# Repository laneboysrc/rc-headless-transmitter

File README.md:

# Smartphone / Web browser configurable RC transmitter

This project implements a 2.4 GHz RC transmitter using the NRF24L01+ wireless module and the STM32F103C8T6 micro-controller.

The term *headless* comes from the IT industry, where a headless system is one that does not provide a user interface itself, but is rather configured remotely. Within this project, *headless* means that the transmitter does not have a display or buttons for configuration. It relies on remote configuration through a web-browser running on a Smartphone, Tablet or computer.

The motivation for this project was to upgrade old AM/FM RC transmitter hardware, and to turn a cheap RC simulator into a fully operational transmitter that supports multiple models.

By keeping the user interface for configuration out of the transmitter, we don't need to perform complicated mechanical modifications to add a display and buttons. We only replace the old electronics with a modern 32 bit ARM micro-controller and a reliable 2.4 GHz transceiver wired on a prototyping board.

The transmitter is currently compatible with HobbyKing HKR3000 and HKR3100 receivers, as well as the [LANE Boys RC nrf24le01-rc](https://github.com/laneboysrc/nrf24l01-rc) DIY receivers. It runs off a 1S Li-Ion battery.

## How it works

The *headless transmitter* works like any low-end 2.4 GHz RC system on the market: power it on, and use it with the model you have it setup for.

However, unlike low-end transmitters, the *headless transmitter* supports advanced features like expo, mixing, failsafe and more.

In order to configure those features, you need to use a web-browser on your Smartphone, Tablet or computer.

To be able to connect your Smartphone to the transmitter, we need to translate between different radio protocols: The transmitter uses a proprietary RF protocol, while the Smartphone supports Wi-Fi. This translation takes place in a small, external box called *configurator*.

When you want to configure your *headless transmitter*, you turn the *configurator* on, connect your phone to the Wi-Fi access-point the *configurator* provides, and launch the configuration web-app to perform the configuration. When you are done, the changes are automatically saved in the transmitter and persist over power cycles.

The *configurator* is built from an **Orange Pi Zero**, with an extra RF module for the connection to the *headless transmitter*.

The Smartphone has a large amount of persistent memory. This allows us to store configurations for multiple models. When we want to reconfigure the transmitter for another model, we simply download the model configuration configuration into the *headless transmitter*. This only takes a few seconds.

The power consumption of the transmitter is low: A single 800 mAh Li-Ion battery keeps the transmitter running for approximately 15 hours. The *configurator* is only used rarely and can be powered from a suitable power bank.

## Cost

When sourcing the modules from China, a transmitter can be built for less than USD 10. The *configurator* hardware cost is less than USD 20. You only need one *configurator*, regardless of how many *headless transmitters* you have.

## Getting started

Please consult the [INSTALL.md](INSTALL.md) file for instructions.

The [docs/](docs) folder contains various documents explaining details for the architecture.

The *headless transmitters* hardware is described in the [transmitter/](transmitter/) folder.

The *configurator* is based on the Orange Pi Zero. Its hardware documentation resides in
[configurator/orangepizero/HARDWARE.md](configurator/orangepizero/HARDWARE.md).

The *web-app* can be accessed from [https://laneboysrc.github.io/rc-headless-transmitter](https://laneboysrc.github.io/rc-headless-transmitter)

## WORK IN PROGRESS

This project is not finished yet. Refer to the [TODO](TODO.md) list for items that we plan to implement in the future.

At the moment the project has only been tested on Android using Chrome and Firefox, and on PCs running Chrome or Firefox.

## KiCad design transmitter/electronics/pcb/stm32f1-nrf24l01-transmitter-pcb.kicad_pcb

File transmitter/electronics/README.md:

This folder contains the schematics and layout of the *headless transmitter* hardware.

[BOM.txt](BOM.txt) contains a list of all components.

The project is made using [KiCad](http://kicad-pcb.org/). For convenience the schematics are also available in [PDF format](stm32f1-nrf24l01-transmitter.pdf).

Note that the PCB designs are not actual circuit board designs, but rather meant to be built on a [Perfboard](https://en.wikipedia.org/wiki/Perfboard).

There are different variants that we adapted to suit different transmitters we modified.

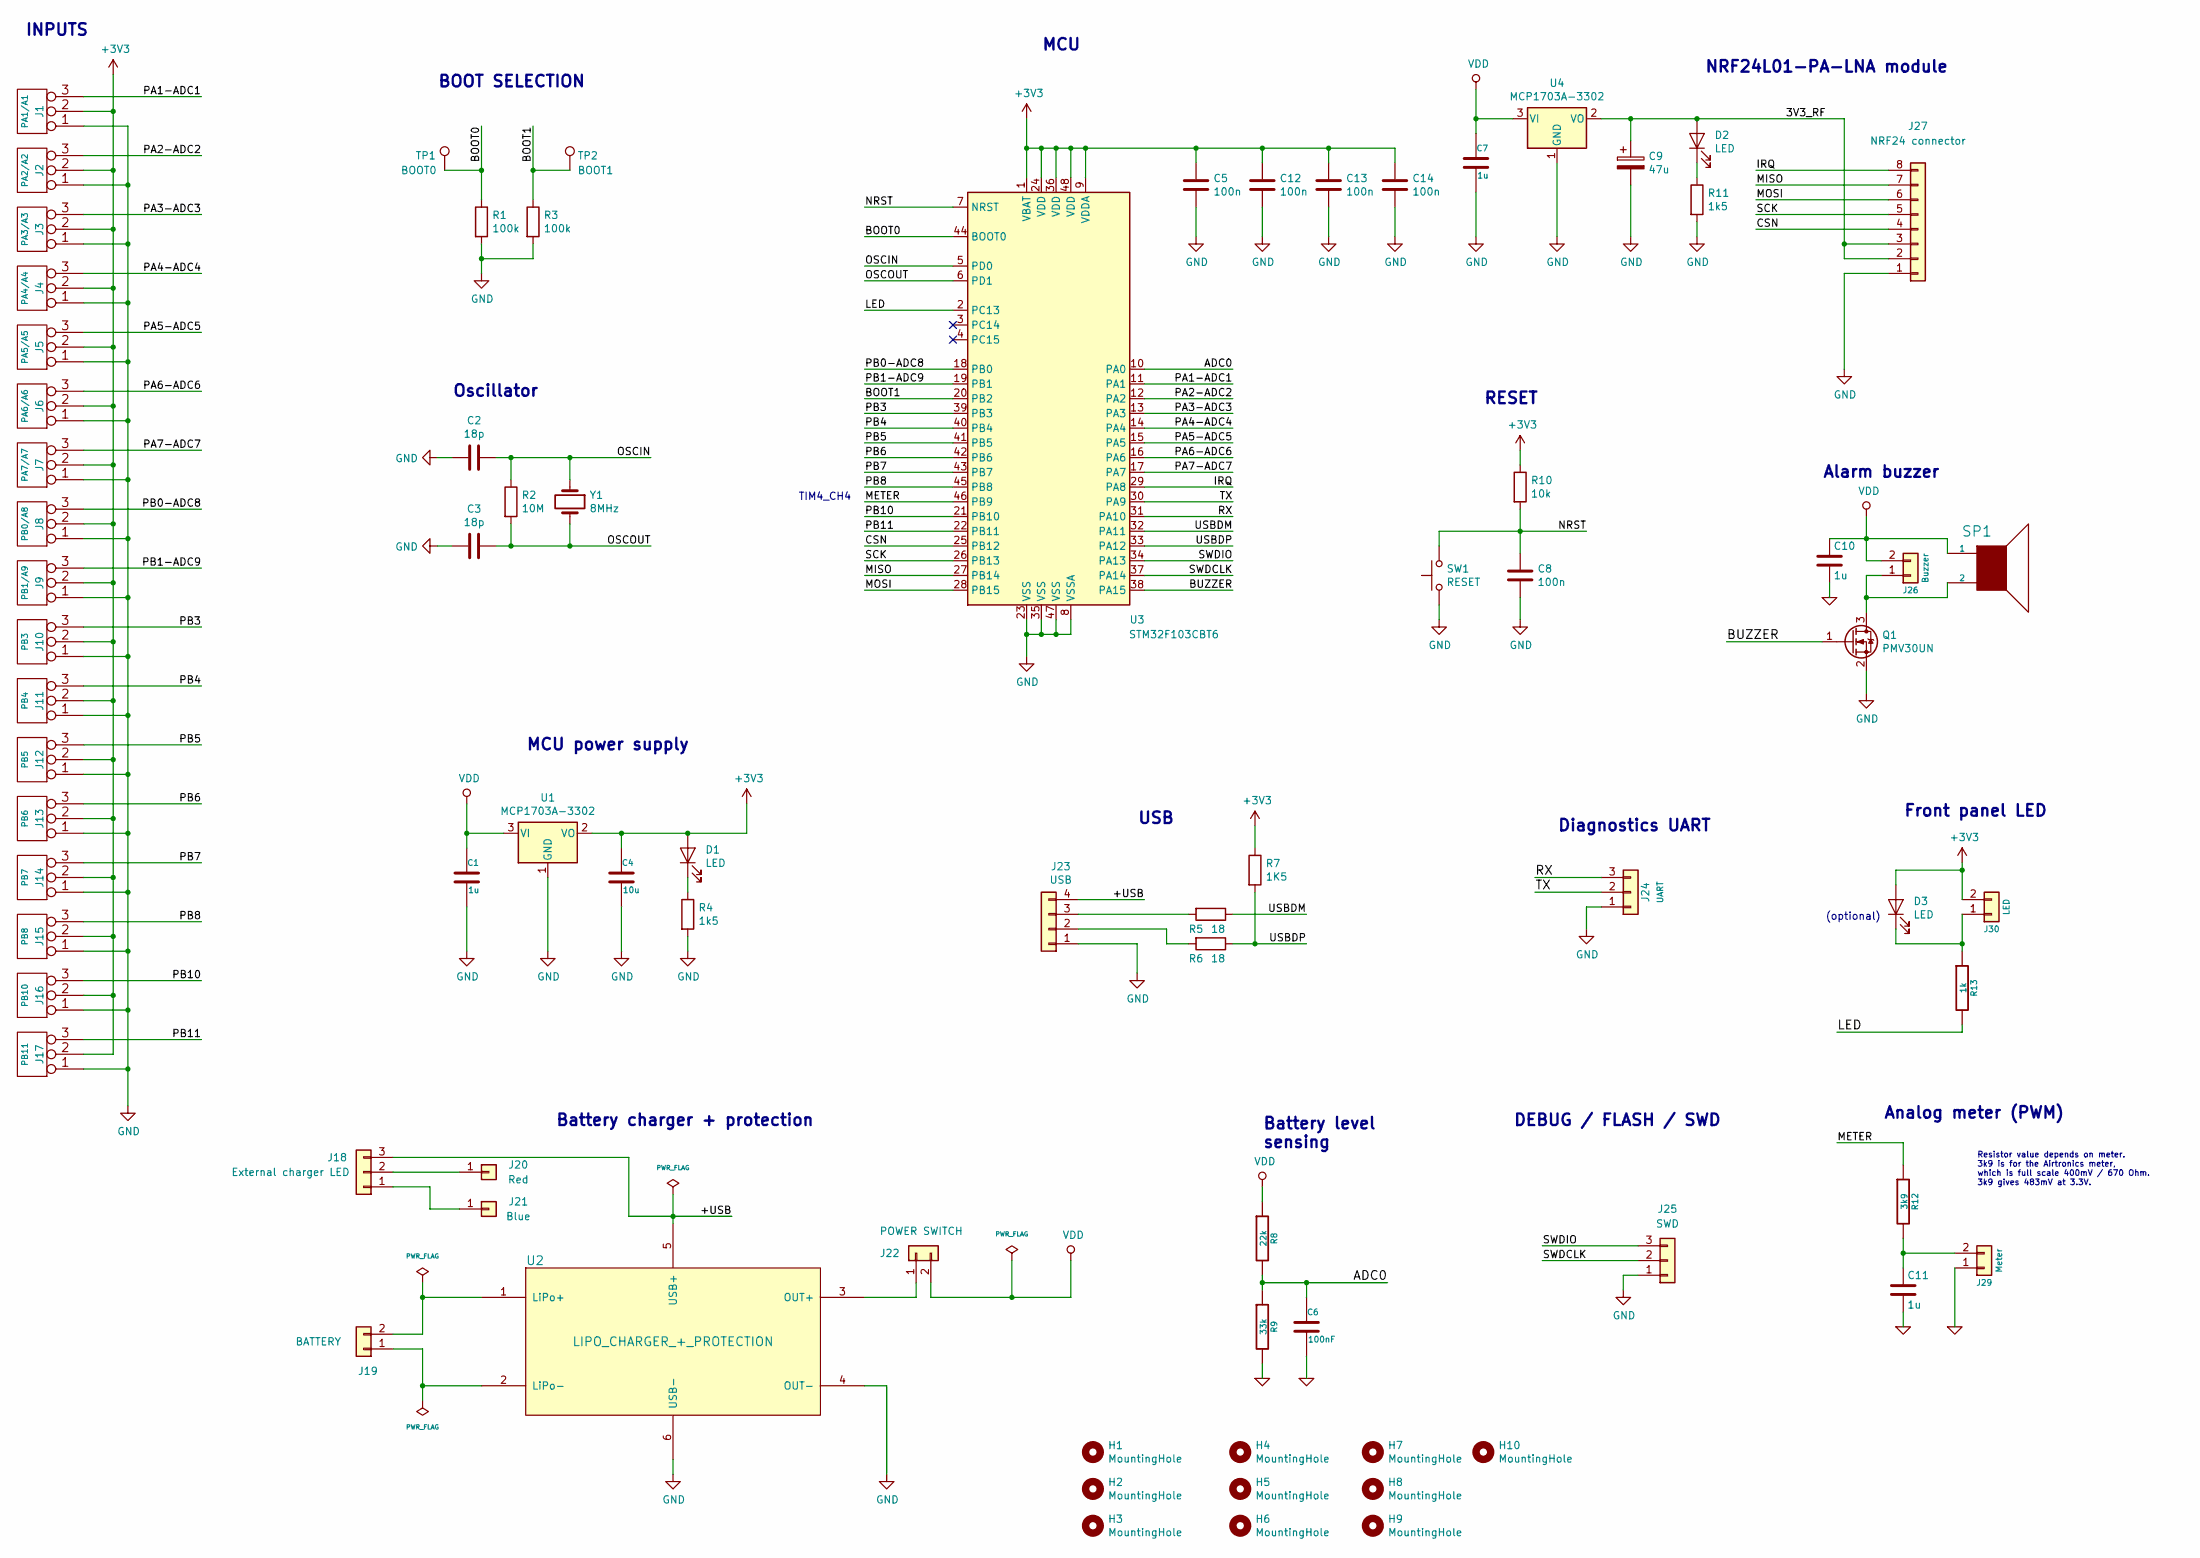
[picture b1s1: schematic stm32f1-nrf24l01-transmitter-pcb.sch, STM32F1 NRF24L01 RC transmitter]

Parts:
C1, C7, C10, C11: 1u; C_0805_2012Metric_Pad1.15x1.40mm_HandSolder
C2, C3: 18p; C_0603_1608Metric_Pad1.05x0.95mm_HandSolder
C4: 10u; C_0805_2012Metric_Pad1.15x1.40mm_HandSolder
C5, C8, C12, C13, C14: 100n; C_0603_1608Metric_Pad1.05x0.95mm_HandSolder
C6: 100nF; C_0805_2012Metric_Pad1.15x1.40mm_HandSolder
C9: 47u; C_0805_2012Metric_Pad1.15x1.40mm_HandSolder
D1, D2, D3: LED; LED_0805_2012Metric_Pad1.15x1.40mm_HandSolder
H1, H2, H3, H9, H10: MountingHole; MountingHole_3.2mm_M3_DIN965
H4, H5, H6, H7, H8: MountingHole; MountingHole_2.7mm_M2.5_DIN965
J1: PA1/A1; JST_XH_B3B-XH-A_1x03_P2.50mm_Vertical
J2: PA2/A2; JST_XH_B3B-XH-A_1x03_P2.50mm_Vertical
J3: PA3/A3; JST_XH_B3B-XH-A_1x03_P2.50mm_Vertical
J4: PA4/A4; JST_XH_B3B-XH-A_1x03_P2.50mm_Vertical
J5: PA5/A5; JST_XH_B3B-XH-A_1x03_P2.50mm_Vertical
J6: PA6/A6; JST_XH_B3B-XH-A_1x03_P2.50mm_Vertical
J7: PA7/A7; JST_XH_B3B-XH-A_1x03_P2.50mm_Vertical
J8: PB0/A8; JST_XH_B3B-XH-A_1x03_P2.50mm_Vertical
J9: PB1/A9; JST_XH_B3B-XH-A_1x03_P2.50mm_Vertical
J10: PB3; JST_XH_B3B-XH-A_1x03_P2.50mm_Vertical
J11: PB4; JST_XH_B3B-XH-A_1x03_P2.50mm_Vertical
J12: PB5; JST_XH_B3B-XH-A_1x03_P2.50mm_Vertical
J13: PB6; JST_XH_B3B-XH-A_1x03_P2.50mm_Vertical
J14: PB7; JST_XH_B3B-XH-A_1x03_P2.50mm_Vertical
J15: PB8; JST_XH_B3B-XH-A_1x03_P2.50mm_Vertical
J16: PB10; JST_XH_B3B-XH-A_1x03_P2.50mm_Vertical
J17: PB11; JST_XH_B3B-XH-A_1x03_P2.50mm_Vertical
J18: External charger LED; JST_XH_B3B-XH-A_1x03_P2.50mm_Vertical
J19: BATTERY; JST_XH_B2B-XH-A_1x02_P2.50mm_Vertical
J20: Red; TestPoint_Pad_1.5x1.5mm
J21: Blue; TestPoint_Pad_1.5x1.5mm
J22: POWER SWITCH; JST_XH_B2B-XH-A_1x02_P2.50mm_Vertical
J23: USB; JST_XH_B4B-XH-A_1x04_P2.50mm_Vertical
J24: UART; PinHeader_1x03_P2.54mm_Vertical
J25: SWD; PinHeader_1x03_P2.54mm_Vertical
J26: Buzzer; JST_XH_B2B-XH-A_1x02_P2.50mm_Vertical
J27: NRF24 connector; JST_XH_B8B-XH-A_1x08_P2.50mm_Vertical
J29: Meter; JST_XH_B2B-XH-A_1x02_P2.50mm_Vertical
J30: LED; JST_XH_B2B-XH-A_1x02_P2.50mm_Vertical
Q1: PMV30UN; SOT-23_Handsoldering
R1, R3: 100k; R_0805_2012Metric_Pad1.15x1.40mm_HandSolder
R2: 10M; R_0805_2012Metric_Pad1.15x1.40mm_HandSolder
R4, R11: 1k5; R_0805_2012Metric_Pad1.15x1.40mm_HandSolder
R5, R6: 18; R_0805_2012Metric_Pad1.15x1.40mm_HandSolder
R7: 1K5; R_0805_2012Metric_Pad1.15x1.40mm_HandSolder
R8: 22k; R_0805_2012Metric_Pad1.15x1.40mm_HandSolder
R9: 33k; R_0805_2012Metric_Pad1.15x1.40mm_HandSolder
R10: 10k; R_0805_2012Metric_Pad1.15x1.40mm_HandSolder
R12: 3k9; R_0805_2012Metric_Pad1.15x1.40mm_HandSolder
R13: 1k; R_0805_2012Metric_Pad1.15x1.40mm_HandSolder
SP1: SPEAKER; MagneticBuzzer_PUI_AT-0927-TT-6-R
SW1: RESET; Tact switch 6x4x3
TP1: BOOT0; TestPoint_Pad_1.5x1.5mm
TP2: BOOT1; TestPoint_Pad_1.5x1.5mm
U1, U4: MCP1703A-3302; SOT-23_Handsoldering
U2: LIPO_CHARGER_+_PROTECTION; LiPo_charger_and_protection
U3: STM32F103CBT6; LQFP-48_7x7mm_P0.5mm
Y1: 8MHz; Crystal_SMD_5032-2Pin_5.0x3.2mm

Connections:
+3V3: C4.1, C5.1, C12.1, C13.1, C14.1, D1.2 (A), D3.2 (A), J1.2 (PM), J2.2 (PM), J3.2 (PM), J4.2 (PM), J5.2 (PM), J6.2 (PM), J7.2 (PM), J8.2 (PM), J9.2 (PM), J10.2 (PM), J11.2 (PM), J12.2 (PM), J13.2 (PM), J14.2 (PM), J15.2 (PM), J16.2 (PM), J17.2 (PM), J30.2, R7.1, R10.1, U1.2 (VO), U3.1 (VBAT), U3.9 (VDDA), U3.24 (VDD), U3.36 (VDD), U3.48 (VDD)
/3V3_RF: C9.1, D2.2 (A), J27.2, J27.3, U4.2 (VO)
/+USB: J18.3, J23.4, U2.5 (USB+)
/ADC0: C6.1, R8.2, R9.1, U3.10 (PA0)
/BOOT0: R1.1, TP1.1, U3.44 (BOOT0)
/BOOT1: R3.1, TP2.1, U3.20 (PB2)
/BUZZER: Q1.1 (G), U3.38 (PA15)
/CSN: J27.4, U3.25 (PB12)
/IRQ: J27.8, U3.29 (PA8)
/LED: R13.2, U3.2 (PC13)
/METER: R12.1, U3.46 (PB9)
/MISO: J27.7, U3.27 (PB14)
/MOSI: J27.6, U3.28 (PB15)
/NRST: C8.1, R10.2, SW1.2, U3.7 (NRST)
/OSCIN: C2.1, R2.1, U3.5 (PD0), Y1.1
/OSCOUT: C3.1, R2.2, U3.6 (PD1), Y1.2
/PA1-ADC1: J1.3, U3.11 (PA1)
/PA2-ADC2: J2.3, U3.12 (PA2)
/PA3-ADC3: J3.3, U3.13 (PA3)
/PA4-ADC4: J4.3, U3.14 (PA4)
/PA5-ADC5: J5.3, U3.15 (PA5)
/PA6-ADC6: J6.3, U3.16 (PA6)
/PA7-ADC7: J7.3, U3.17 (PA7)
/PB0-ADC8: J8.3, U3.18 (PB0)
/PB1-ADC9: J9.3, U3.19 (PB1)
/PB3: J10.3, U3.39 (PB3)
/PB4: J11.3, U3.40 (PB4)
/PB5: J12.3, U3.41 (PB5)
/PB6: J13.3, U3.42 (PB6)
/PB7: J14.3, U3.43 (PB7)
/PB8: J15.3, U3.45 (PB8)
/PB10: J16.3, U3.21 (PB10)
/PB11: J17.3, U3.22 (PB11)
/RX: J24.3, U3.31 (PA10)
/SCK: J27.5, U3.26 (PB13)
/SWDCLK: J25.2, U3.37 (PA14)
/SWDIO: J25.3, U3.34 (PA13)
/TX: J24.2, U3.30 (PA9)
/USBDM: R5.1, U3.32 (PA11)
/USBDP: R6.1, R7.2, U3.33 (PA12)
GND: C1.2, C2.2, C3.2, C4.2, C5.2, C6.2, C7.2, C8.2, C9.2, C10.2, C11.2, C12.2, C13.2, C14.2, J1.1, J2.1, J3.1, J4.1, J5.1, J6.1, J7.1, J8.1, J9.1, J10.1, J11.1, J12.1, J13.1, J14.1, J15.1, J16.1, J17.1, J23.1, J24.1, J25.1, J27.1, J29.1, Q1.2 (S), R1.2, R3.2, R4.2, R9.2, R11.2, SW1.1, U1.1 (GND), U2.4 (OUT-), U2.6 (USB-), U3.8 (VSSA), U3.23 (VSS), U3.35 (VSS), U3.47 (VSS), U4.1 (GND)
unnamed: C11.1, J29.2, R12.2
unnamed: D1.1 (K), R4.1
unnamed: D2.1 (K), R11.1
unnamed: D3.1 (K), J30.1, R13.1
unnamed: J18.1, J21.1
unnamed: J18.2, J20.1
unnamed: J19.1, U2.2 (LiPo-)
unnamed: J19.2, U2.1 (LiPo+)
unnamed: J22.1, U2.3 (OUT+)
unnamed: J23.2, R6.2
unnamed: J23.3, R5.2
unnamed: J26.1, Q1.3 (D), SP1.2
VDD: C1.1, C7.1, C10.1, J22.2, J26.2, R8.1, SP1.1, U1.3 (VI), U4.3 (VI)

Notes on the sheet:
Diagnostics UART
Front panel LED
Alarm buzzer
Analog meter (PWM)
Resistor value depends on meter. 3k9 is for the Airtronics meter, which is full scale 400mV / 670 Ohm. 3k9 gives 483mV at 3.3V.
USB
Battery level sensing
TIM4_CH4
(optional)
BOOT SELECTION
INPUTS
MCU
NRF24L01-PA-LNA module
MCU power supply
Battery charger + protection
Oscillator
RESET
DEBUG / FLASH / SWD

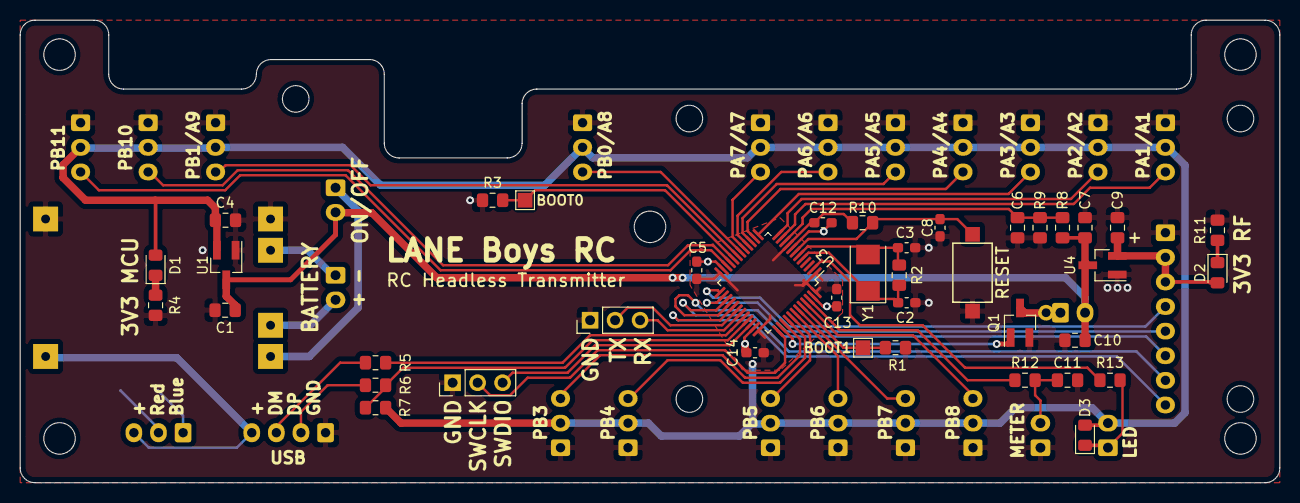
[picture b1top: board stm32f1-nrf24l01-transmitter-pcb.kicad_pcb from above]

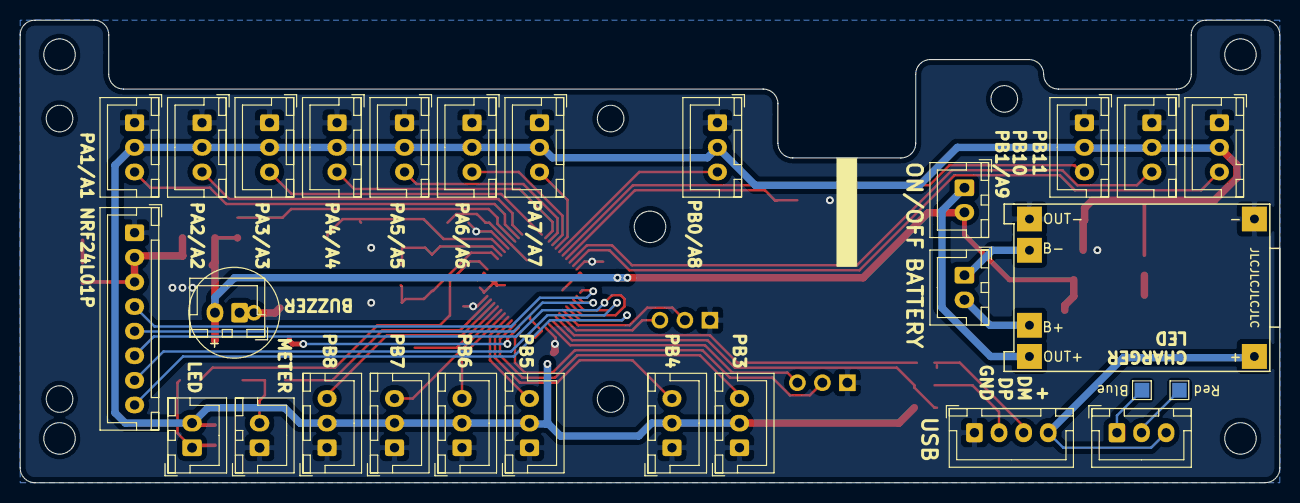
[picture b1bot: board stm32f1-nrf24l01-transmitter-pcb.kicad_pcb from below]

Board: 2 copper layers, 128.0 x 47.0 mm, 79 parts (29 on the bottom side), 54 nets.

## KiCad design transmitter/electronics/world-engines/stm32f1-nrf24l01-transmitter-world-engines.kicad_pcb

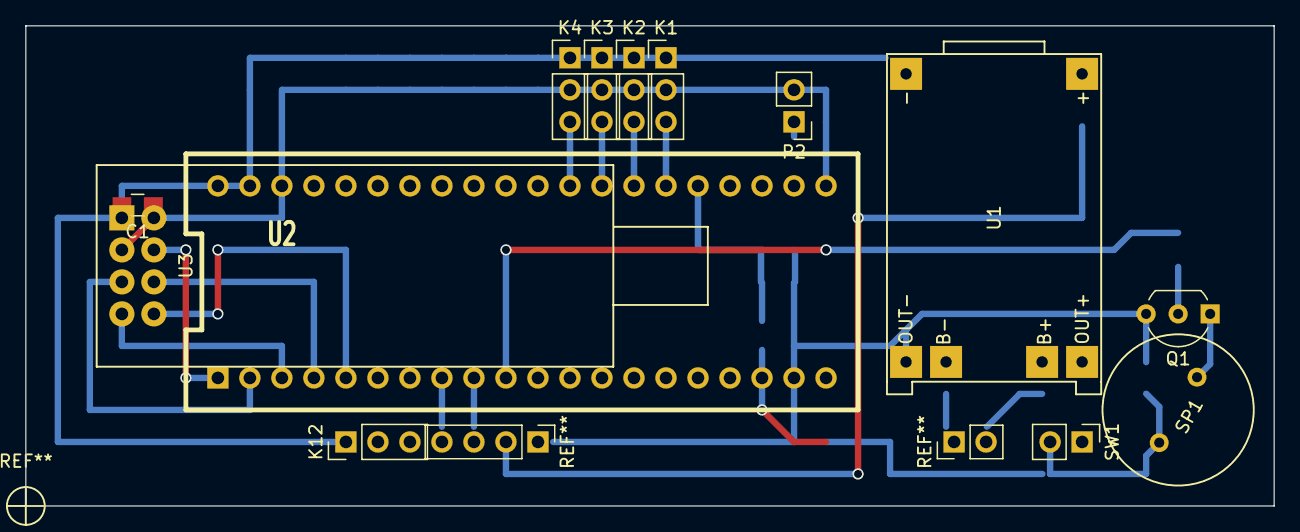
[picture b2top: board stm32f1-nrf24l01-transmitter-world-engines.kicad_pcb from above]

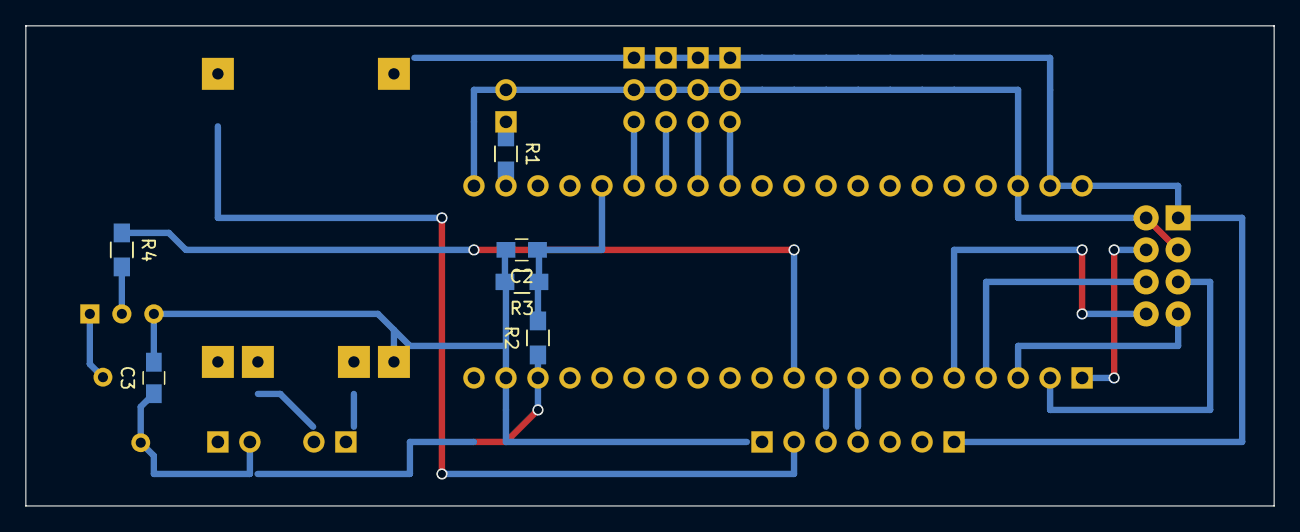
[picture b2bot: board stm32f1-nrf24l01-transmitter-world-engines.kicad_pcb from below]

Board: 2 copper layers, 99.1 x 38.1 mm, 19 parts (6 on the bottom side), 21 nets.

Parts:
C1, C3: 1u; C_0805_HandSoldering
C2: 100nF; C_0805_HandSoldering
K1, K2, K3, K4: CONN_3; Pin_Header_Straight_1x03_Pitch2.54mm
K12: UART; Pin_Header_Straight_1x03_Pitch2.54mm
P2: LED; Pin_Header_Straight_1x02_Pitch2.54mm
Q1: BC547B; TO-92_Inline_Wide
R1, R4: 1k; R_0805_HandSoldering
R2: 22k; R_0805_HandSoldering
R3: 33k; R_0805_HandSoldering
SP1: SPEAKER; Buzzer_passive
SW1: ON/OFF; Pin_Header_Straight_1x02_Pitch2.54mm
U1: LIPO_CHARGER_+_PROTECTION; LiPo_charger_and_protection
U2: STM32F103C8T6_DEV_BOARD; STM32F103C8T6
U3: NRF24L01P; NRF24L01P-PA-LNA

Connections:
/ADC0: C2.1, R2.2, R3.1, U2.25
/BUZZER: R4.1, U2.10
/CSN: U2.1, U3.4
/IRQ: U2.5, U3.8
/LED: R1.2, U2.22
/MISO: U2.3, U3.7
/MOSI: U2.4, U3.6
/PA1/ADC1: K1.3, U2.26
/PA2/ADC2: K2.3, U2.27
/PA3/ADC3: K3.3, U2.28
/PA4/ADC4: K4.3, U2.29
/RX: K12.2, U2.7
/SCK: U2.2, U3.5
/TX: K12.3, U2.6
GND: C1.2, C2.2, C3.2, K1.1, K2.1, K3.1, K4.1, K12.1, Q1.3, R3.2, U1.4, U2.19, U2.39, U2.40, U3.1
unnamed: P2.1, R1.1
unnamed: Q1.1, SP1.2
unnamed: Q1.2, R4.2
unnamed: SW1.1, U1.3
VCC: C1.1, K1.2, K2.2, K3.2, K4.2, P2.2, U2.21, U2.38, U3.2, U3.3
VDD: C3.1, R2.1, SP1.1, SW1.2, U2.18

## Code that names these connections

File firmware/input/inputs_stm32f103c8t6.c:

// Inputs available on the AliExpress STM32F103C8T6 board

#include <libopencm3/stm32/gpio.h>

#include <inputs.h>


const uint8_t adc_channel_selection[NUMBER_OF_ADC_CHANNELS] = {1, 2, 3, 4, 5, 6, 7, 8, 9, 0, 17};


const pcb_input_t pcb_inputs[MAX_TRANSMITTER_INPUTS] = {
    // Note: ADC0 is used for measuring the battery voltage, therefore it does
    // not appear in this list

    {.type = ANALOG_DIGITAL, .gpioport = GPIOA, .gpio = GPIO1, .adc_channel = 1,
     .pin_name = "PA1/ADC1"},

    {.type = ANALOG_DIGITAL, .gpioport = GPIOA, .gpio = GPIO2, .adc_channel = 2,
     .pin_name = "PA2/ADC2"},

    {.type = ANALOG_DIGITAL, .gpioport = GPIOA, .gpio = GPIO3, .adc_channel = 3,
     .pin_name = "PA3/ADC3"},

    {.type = ANALOG_DIGITAL, .gpioport = GPIOA, .gpio = GPIO4, .adc_channel = 4,
     .pin_name = "PA4/ADC4"},

    {.type = ANALOG_DIGITAL, .gpioport = GPIOA, .gpio = GPIO5, .adc_channel = 5,
     .pin_name = "PA5/ADC5"},

    {.type = ANALOG_DIGITAL, .gpioport = GPIOA, .gpio = GPIO6, .adc_channel = 6,
     .pin_name = "PA6/ADC6"},

    {.type = ANALOG_DIGITAL, .gpioport = GPIOA, .gpio = GPIO7, .adc_channel = 7,
     .pin_name = "PA7/ADC7"},

    {.type = ANALOG_DIGITAL, .gpioport = GPIOB, .gpio = GPIO0, .adc_channel = 8,
     .pin_name = "PB0/ADC8"},

    {.type = ANALOG_DIGITAL, .gpioport = GPIOB, .gpio = GPIO1, .adc_channel = 9,
     .pin_name = "PB1/ADC9"},

    {.type = DIGITAL, .gpioport = GPIOB, .gpio = GPIO3,
     .pin_name = "PB3"},

    {.type = DIGITAL, .gpioport = GPIOB, .gpio = GPIO4,
     .pin_name = "PB4"},

    {.type = DIGITAL, .gpioport = GPIOB, .gpio = GPIO5,
     .pin_name = "PB5"},

    {.type = DIGITAL, .gpioport = GPIOB, .gpio = GPIO6,
     .pin_name = "PB6"},

    {.type = DIGITAL, .gpioport = GPIOB, .gpio = GPIO7,
     .pin_name = "PB7"},

    {.type = DIGITAL, .gpioport = GPIOB, .gpio = GPIO8,
     .pin_name = "PB8"},

    {.type = DIGITAL, .gpioport = GPIOB, .gpio = GPIO9,
     .pin_name = "PB9"},

    {.type = DIGITAL, .gpioport = GPIOB, .gpio = GPIO10,
     .pin_name = "PB10"},

    {.type = DIGITAL, .gpioport = GPIOB, .gpio = GPIO11,
     .pin_name = "PB11"}
};

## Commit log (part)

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2016-09-11 Move transmitter schematic into subdirectory
2016-09-11 Use Last-Modified HTTP header based on metadata created when making the SPIFFS image
2016-09-12 Remove FIXME text
2016-09-12 Revert to bare DLG configuration
2016-09-15 Update documentation and delete obsolete files
2016-09-16 Add licenses
2016-09-16 Move battery life test stuff to documentation
2016-09-16 Various edits
2016-09-16 Add minor TODO items after reviewing
2016-09-16 Add PDF for schematics
2016-09-16 Add instructions about cloing the project
2016-09-16 Make initial firmware configuration an unconfigured transmitter
2016-09-18 Add TODO re moving LoadDevice
2016-09-20 Improve documentation
2016-09-21 Use 'headless transmitter' consistently in documentation
2016-10-20 Add web components idea
2016-10-26 Add curve view to mixer_unit page
2016-10-26 Change mixer curve preview color to orange
2016-10-27 Center curve on screen and make fine adjust dialog close when pressing Enter
2016-10-28 Remove file that should not be there ...
2016-10-28 Log restore messages to page
2016-11-01 Add Sortable to todo for rearranging mixer units
2016-11-04 Update TODO with offline mode, github.io
    Based on insights gained through studying the Amazon Echo web app
2016-11-04 Store data as Array, not Object, in the backup JSON
2016-11-04 Remove Roboto font
    On Android it is available anyway, and on the PC we just use
    the default sans-serif font. No need to drag along so much data
    for little gain.
2016-11-04 Remove Uint8Array being stored as object
2016-11-04 Make offline mode work
    Using sw-precache module and the related webpack plugin to create
    the service worker.
2016-11-04 Make images, CSS and fonts separate files instead of embedding
    Let the browser do the work... The app size becomes significantly
    smaller and the service worker caches everything anyway
2016-11-04 Add credits update
2016-11-04 Open Github link in a new window
2016-11-04 Use service worker registration script from Google
    This will allow us to notify the user when the app is available
    offline and it has been updated.
2016-11-05 Limit to two packets in flight over the websocket
    If we are sending packets too quickly, the browser combines multiple
    WebSocket packets in one TCP packet. It seems that the ESP Async
    Websocket library can not handle that and silently ignores
    the packet, resulting in lost data.
    The work-around is to send packets slowly for now. Not ideal,
    but at least works.
2016-11-05 Change image file name length to <32 to work with SPIFFS
2016-11-05 Move production build output to /docs/ for github.io
    Add a README in case people look for documentation.
    Make all links relative.
2016-11-05 Update offline mode items
2016-11-05 Improve manifest and icons
2016-11-05 Add battery warning indicator
2016-11-05 Add strftime js library
2016-11-05 Link credits to Github page
    This way we have a single place where gather them
2016-11-05 Show yellow warning when battery voltage of transmitter is low
2016-11-05 Move device load function from DeviceList to Device
2016-11-05 Move addEventListeners from init() to constructor
2016-11-05 Remove issue with YT and Blog not working when connected to the configurator
2016-11-05 Tidy-up addEventListeners
2016-11-05 Make Snackbar a Utils function shared across everywhere
2016-11-07 Update production configurator
2016-11-08 Add initial files for Raspberry Pi based bridge
2016-11-08 Fix mixer curve going outside of grid
2016-11-09 Update service-worker, not sure why it didn't regenerate last time
2016-11-09 Add messages for service worker actions
2016-11-09 Offline mode done; Add need to test Raspi docs
2016-11-11 Update release build with improved min/max
2016-11-11 Add documentation task ESP vs Raspi
2016-11-11 Discuss Raspberry Pi based configurator
2016-11-12 Add hint for slider fine-adjustment
2016-11-12 Speed up bridge detection
2016-11-12 Clear restore log on entry and restore
2016-11-14 Parse and save manually entered RF address and hop channels
2016-11-15 Make ESP Wi-Fi configurable through a text file in the SPIFFS image
2016-11-20 Delay writing persistent storage to flash while configurator is active
    Writing to the flash causes long delays in CPU execution, which in
    turn makes the 5 ms RF timer unreliable, causing the hop sequence
    to become out of sync and the configurator loosing connection.
2017-01-29 Add annotation to Wi-Fi config
2017-02-08 Add buzzer and 3D images
2017-02-09 Update schematics
    - Convert to KiCAD 4.05
    - Dummy links accross battery connector for routing purpos
    - Dummy connector for speaker
2017-02-09 Add list of mods to convert the Jomac Comando Mach 3 transmitter
2017-02-11 Fix switch connector overlapping with charger
2017-02-11 Fix transistor footprint, add decoupling cap for buzzer, minor tweaks
2017-02-12 Add some lessons learned
2017-02-17 Add docs/last-modified to ignore list
2017-02-17 Use the STM32 device unique number as transmitter UUID
    This way every hardware automatically has a unique number, which
    automatically persists during firmware update.
    So we can now update the firmware, and then connect to the
    configurator and the last hardware configuration will automatically
    be restored!
2017-02-18 Make end-point adjustment work regardless of pot polarity
2017-02-20 Use libopencm3 function to retrieve unique ID for better portability
2017-03-19 Add PCB draft for Airtronics transmitter
2017-03-19 Make PCB smaller and annotate
2017-03-20 Add analog meter output to electronics
2017-03-23 Add info about Airtronics meter
2017-03-27 Start on analog meter support
2017-04-01 Add UI for analog battery meter adjustment
2017-04-02 Update configurator app with analog battery meter configuration
2017-04-02 Add spinkit to credits
2017-04-02 Add gh-pages to ignore list
2017-04-02 Fix issue with unlinkSync failing if serviceWorker file does not exist
2017-04-02 Move /documents back to /docs
2017-04-14 Use empty GNU_INSTALL_ROOT by default
2017-05-12 Enable MAX_PACKETS_IN_TRANSITS and make NRF log human readable
2017-05-12 Add TODO items related to nRF UART bridge
2017-05-12 Increase timeout for testing
2017-05-12 Change timeout back to 600ms, did not change anything
2017-05-12 Fix localost->localhost
2017-05-12 Add FIXME items for performance improvement
    Hopefully removing ws-message will improve performance
    on Chrome for Android.
2017-05-12 Get TX_INFO frames directly to Device.onLiveMessage instead of via event
2017-05-13 Remove bind to speed things up
2017-05-13 Convert websocket from binary to text data
    For decoding binary data, we have to use FileReader. FileReader is
    however very slow on Chrome, causing problems. We are therefore
    using hex-encoded strings instead, which is fast on every platform
2017-05-13 Update TODO items after testing
2017-05-13 Add program to shut down the Orange Pi Zero if button is pressed
2017-05-13 Add dist directory containing firmware images
2017-05-13 Fix path to firmware
2017-05-13 Add documentation for Orange Pi Zero pinout
2017-05-14 Remove ESP8266 based bridge, rather use Orange Pi Zero
2017-05-14 Add sample config files for Orange Pi Zero
2017-05-14 Move all transmitter related folders into transmitter/
    This tidies up things quite a bit
2017-05-14 Rename dist to bin/
2017-05-14 Rename hostapd.conf file so it does not clash with repository default file
    Instead we use our own file and point /etc/default/hostapd to it
2017-05-14 Move script out of orphan directory
2017-05-15 Add script to update all dependencies
2017-05-15 Add label for Orange Pi Zero 3D printed case
2017-05-16 Remove obsolete Raspberry Pi references
2017-05-16 Remove ESP8266 hardware
2017-05-16 Update repository
2017-05-16 Add to-do regarding throttle
2017-05-16 Minor clean-up
2017-05-16 More documentation improvements
2017-05-16 Move WebSocket to wss://192.168.4.1/ws
    This makes it easier to access from all browsers, regarding
    creation of security exceptions for the self-signed certificate
2017-05-16 Update new websocket location
2017-05-17 Add hints when bridge can not connect
2017-05-18 Add timeout before starting openocd
    Sometimes openocd failed due to accessing the GPIOs before
    udev had a chance to apply the correct group
2017-05-18 Fix spelling in link
2017-05-19 Add the Git commit version and date to the web-app about page
2017-05-19 Add noscript tag in case JS is disabled
2017-05-19 Add alt tag to image
2017-05-19 Add target _blank to certificate test link
2017-05-19 Add updated config file
    Includes Durga and all 4 transmitters
2017-05-21 Add Futaba FP-2F analog meter information
2017-05-22 Show error message when opening indexedDB fails
2017-05-23 Add info about ST-DR
2017-05-24 Fix mixer multiplication
    We must apply multiplication before division, as we are working
    with Integers
2017-05-24 Update transmitter binary
    Contains mixer multiplication fix
2017-06-02 Start making the web-app work on Windows 7 / IE11
    Still issue with missing <template> tag support
2017-06-02 Fix /button instead of /a
2017-06-02 More IE11 polyfills
    Still not working, but better
2017-07-24 Remove location.has from redirect to fix offline
2017-11-04 Add documentation of how to compile .INO files
2018-05-29 Add photos of the Orange Pi Zero with nRF51 bridge
2018-06-30 Change RAM size to 16KB so that new CORE51822 with QFAA chip can be used
2018-08-07 Add support for the LANEBoysRC 4-channel protocol
    Modded version of the HK310 protocol.
2018-08-07 Add protocol documentation
2018-08-19 Add backup for latest configuration
2018-08-20 Move packet creation functions into device.js
2018-08-20 Rebuild using release code
2018-08-21 Add LED blinking and prepare to use USART3 for diagnostics
2018-08-21 Make control transfer filter work and add WebUSB test code
2018-08-23 Implement UART to USB communication
2018-08-24 Implement LED flashing to show activity
2018-08-24 Add SLIP encoding/decoding utility
2018-08-24 Rename ws_protocol to websocket_transport
2018-08-24 Make async work
2018-08-25 Force re-upload of working version
2018-08-26 Make websocket work again
2018-08-27 Show hint only for Wi-Fi, show USB pair button only for WebUSB
2018-08-27 Open USB device after pairing
2018-08-28 Tidy up the console log
2018-08-30 Move packet cache into device
2018-08-30 Add WebUSB support
2018-09-01 Make fine adjustments of sensible granularity
2018-09-02 Make WebUSB the default
2018-09-02 Add configuration backup that includes the Topsky DLG
2018-10-19 Add LANE Boys RC 8ch protocol support
2018-11-04 Fix 8ch protocol to output proper data range
2018-11-08 Fix warning message due to updated libopencm3
2018-11-08 Change device descriptor
2018-11-08 Prepare for multiple configurator transports
2018-11-08 Start debugging WebUSB transport
2018-11-09 Discard packets in transit on every received message
    Before we did not discard on INFO messages, which caused
    issues right after connecting when there was not other
    packet and the send logic got stuck
2018-11-09 Re-enable WFI and enable USB interrupt
2018-11-09 Use external HSE clock with 48 MHz system clock
    The AHB clocks run the same as before, but the system clock is
    now 48 MHz for USB purpose
2018-11-16 Send ADC9 via INFO packet to configurator
2018-11-16 Fix clock tree, now USB and sounds are working fine
2018-12-20 Add latest configuration with World Engines and Heathkit
2018-12-20 Fix comment about channel values
2019-02-04 Add switch mount for Devo 4
2019-02-05 Modify Devo4 button mount
2019-02-06 Add antenna mount for Devo 4
2019-03-14 Update for other antenna
2019-04-16 Implement live hardware inputs display
2019-04-17 Add model and transmitter backup
2019-04-18 Remove slider style when at minimum value
2019-09-15 Add recent backup
2020-01-17 Clean up electronics for latest KiCad
2020-01-20 Work on schematics and layout
2020-01-21 Work on layout
2020-01-26 Make combined PCB
2020-01-27 Add JLC fabrication marker
2020-01-28 Fix DRC issue and add keepout area
2020-01-29 Move components out of connector courtyard
2020-01-29 Tweak MCU power supply
2020-02-12 Add Gerber as sent off for fabrication
    NOTE: Component labels are missing from silk screen
2020-02-26 Add Graupner Antenna guide
2020-02-28 Add more Graupner E8 parts
2020-03-04 Add Windows 7 driver
